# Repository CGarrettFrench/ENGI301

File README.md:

<h1>ENGI301</h1>
Repository for ENGI301 coursework

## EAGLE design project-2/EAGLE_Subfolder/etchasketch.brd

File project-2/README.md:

# ENGI 301 Project 02
# Garrett French
# ENGI 301 F22

This folder contains my submission for Project 02 for ENGI 301 F22, which is a design of a PCB board for a standard Etch-a-Sketch developed on a PocketBeagle platform. Within this folder is a .pdf file of my schematic ("schematicpdf"), the Bill of Materials for my design ("etchasketchBOM"), an "mfg" sub-folder containing my manufacturing gerber files generated by Eagle, a "docs" sub-folder containing my mechanical diagram and screenshots of the top and bottom layer of my PCB board, and finally, an "EAGLE_Subfolder" sub-folder which contains the Eagle files for this design - the schematic, library, board, and design rules files.

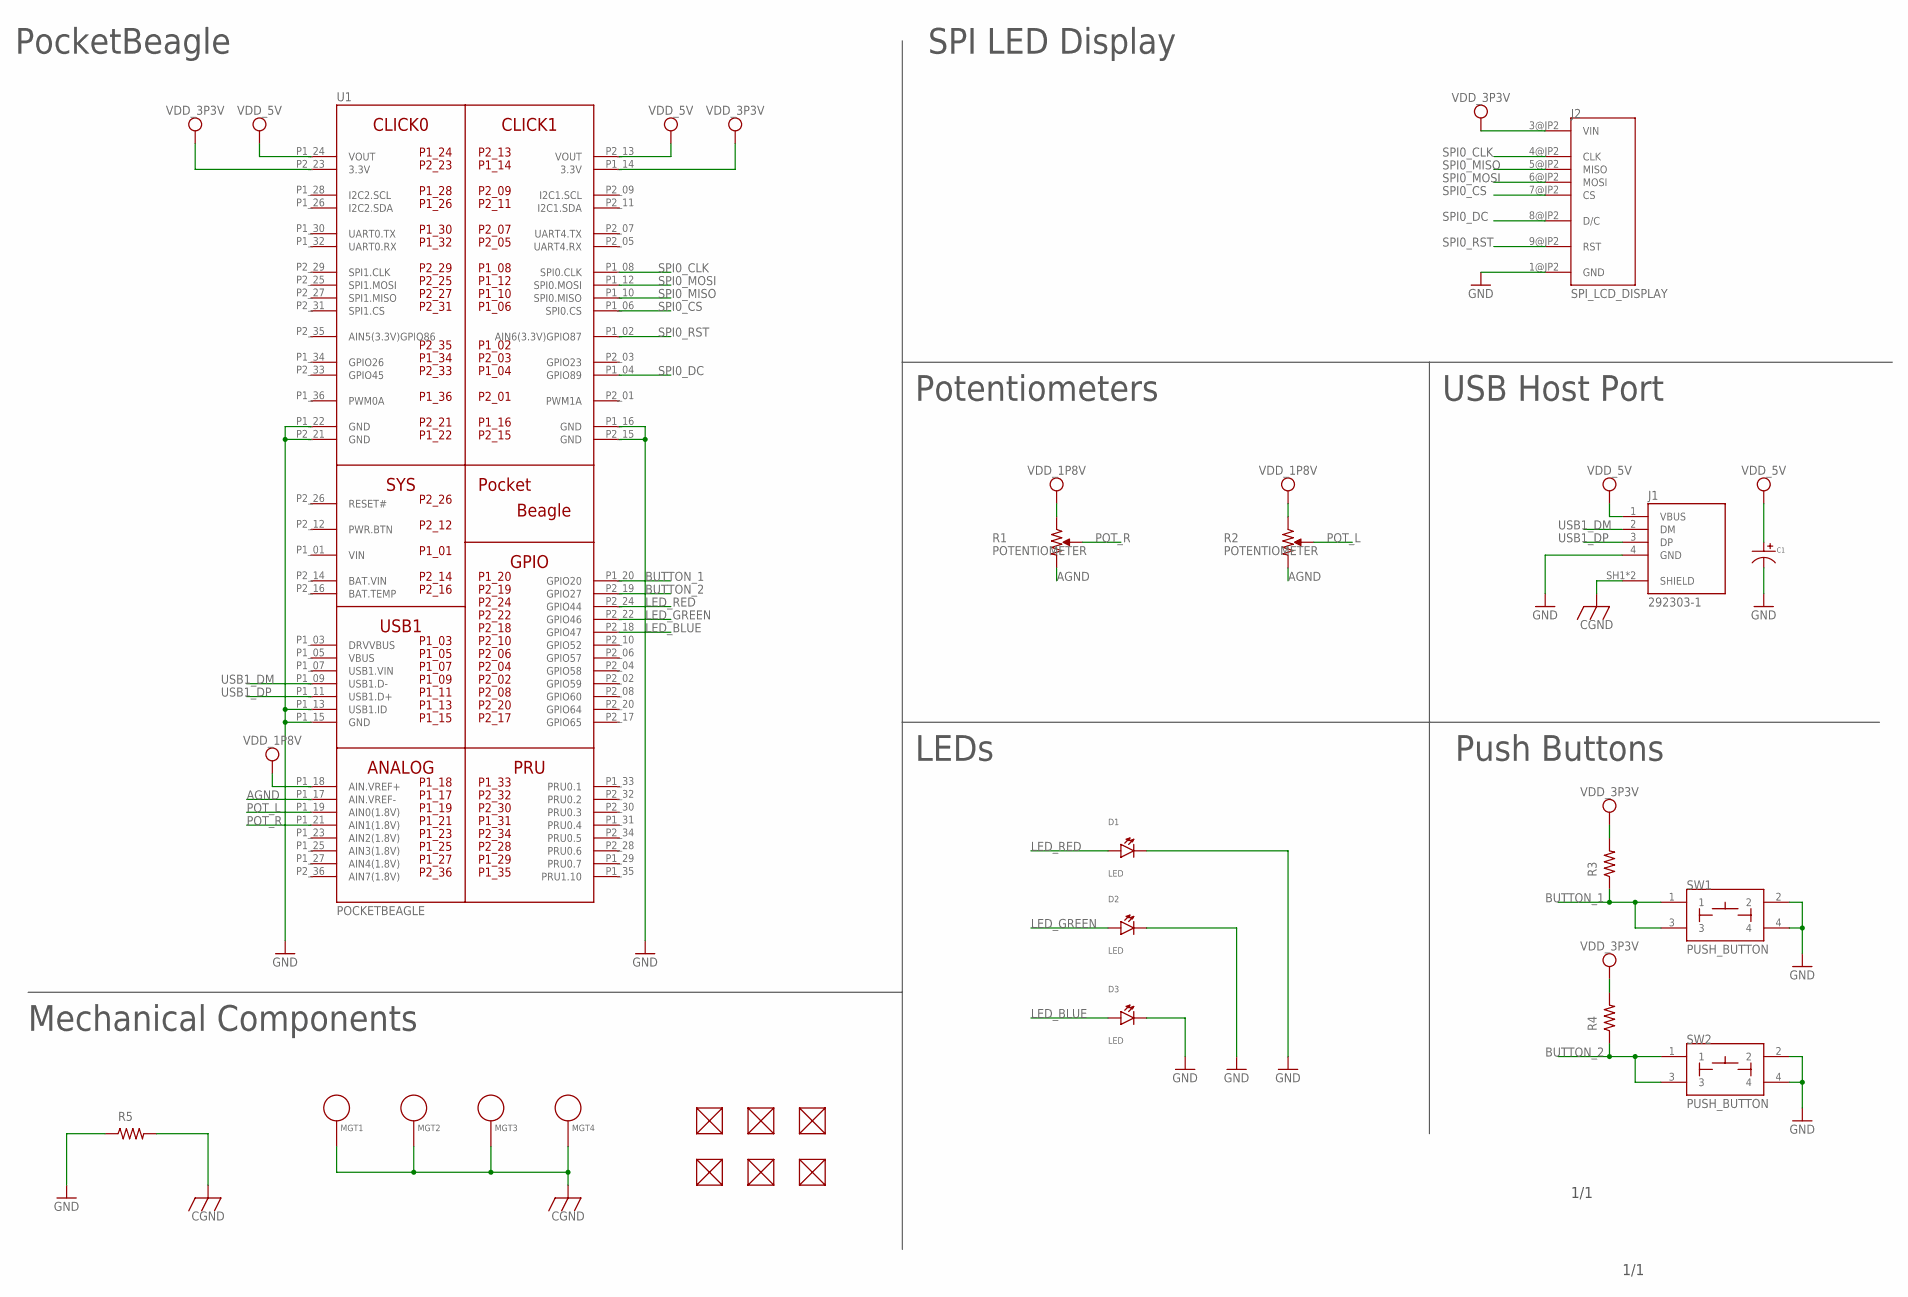
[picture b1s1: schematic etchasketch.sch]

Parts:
C1: CAPACITOR_P_10MM; CP10MM
D1, D2, D3: LED; EIA-STD
FUD1, FUD2, FUD3, FUD4, FUD5, FUD6: FIDUCIAL; FIDUCIAL_40MIL
J1: 292303-1; TE_292303-1
J2: SPI_LCD_DISPLAY; TFT_LCD_PCB
MGT1, MGT2, MGT3, MGT4: MOUNTING_HOLE
R1, R2: POTENTIOMETER; POT-PO90S
R3, R4, R5: R_R0603; R0603
SW1, SW2: PUSH_BUTTON; BUTTON_12.5MM
U1: POCKETBEAGLE

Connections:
AGND: R1.CW, R2.CW, U1.P1_17 (AIN.VREF-)
BAT.VIN: U1.P2_14 (BAT.VIN)
BUTTON_1: R3.1, SW1.1, SW1.3, U1.P1_20 (GPIO20)
BUTTON_2: R4.1, SW2.1, SW2.3, U1.P2_19 (GPIO27)
CGND: J1.SH1 (SHIELD), J1.SH2 (SHIELD), MGT1.P$1, MGT2.P$1, MGT3.P$1, MGT4.P$1, R5.2
GND: C1.P$2, D1.CATHODE, D2.CATHODE, D3.CATHODE, J1.4 (GND), J2.1@JP2 (GND), R5.1, SW1.2, SW1.4, SW2.2, SW2.4, U1.P1_13 (USB1.ID), U1.P1_15 (GND), U1.P1_16 (GND), U1.P1_22 (GND), U1.P2_15 (GND), U1.P2_21 (GND)
LED_BLUE: D3.ANODE, U1.P2_18 (GPIO47)
LED_GREEN: D2.ANODE, U1.P2_22 (GPIO46)
LED_RED: D1.ANODE, U1.P2_24 (GPIO44)
POT_L: R2.S, U1.P1_19 (AIN0(1.8V))
POT_R: R1.S, U1.P1_21 (AIN1(1.8V))
SPI0_CLK: J2.4@JP2 (CLK), U1.P1_08 (SPI0.CLK)
SPI0_CS: J2.7@JP2 (CS), U1.P1_06 (SPI0.CS)
SPI0_DC: J2.8@JP2 (D/C), U1.P1_04 (GPIO89)
SPI0_MISO: J2.5@JP2 (MISO), U1.P1_10 (SPI0.MISO)
SPI0_MOSI: J2.6@JP2 (MOSI), U1.P1_12 (SPI0.MOSI)
SPI0_RST: J2.9@JP2 (RST), U1.P1_02 (AIN6(3.3V)GPIO87)
USB1_DM: J1.2 (DM), U1.P1_09 (USB1.D-)
USB1_DP: J1.3 (DP), U1.P1_11 (USB1.D+)
VDD_1P8V: R1.CCW, R2.CCW, U1.P1_18 (AIN.VREF+)
VDD_3P3V: J2.3@JP2 (VIN), R3.2, R4.2, U1.P1_14 (3.3V), U1.P2_23 (3.3V)
VDD_5V: C1.P$1, J1.1 (VBUS), U1.P1_24 (VOUT), U1.P2_13 (VOUT)
VIN: U1.P1_01 (VIN)

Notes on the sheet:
PocketBeagle
SPI LED Display
Potentiometers
USB Host Port
Push Buttons
LEDs
Mechanical Components
1/1

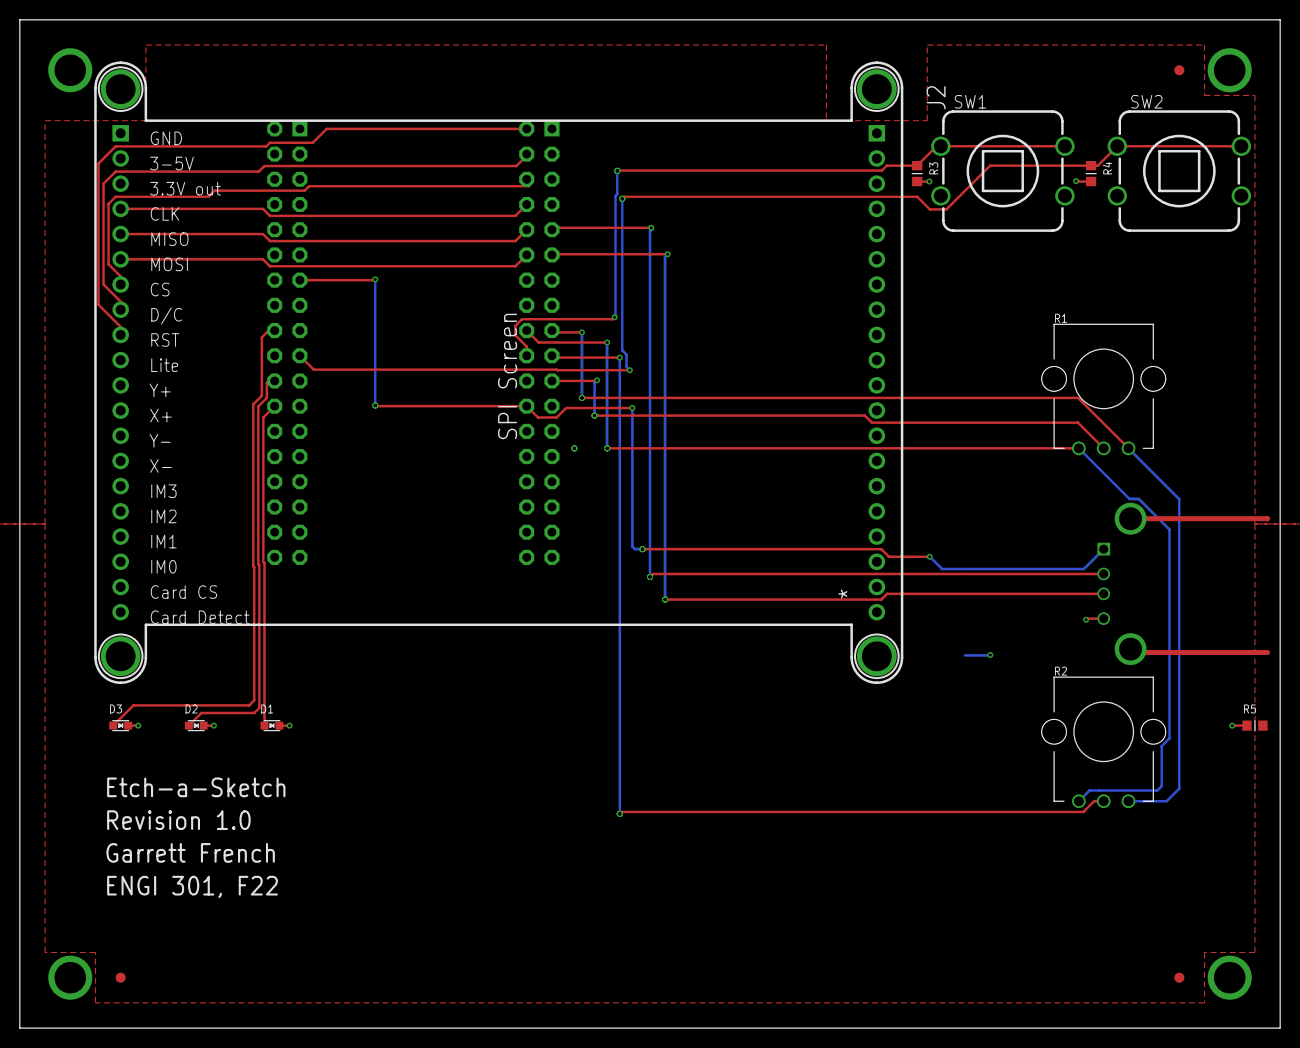
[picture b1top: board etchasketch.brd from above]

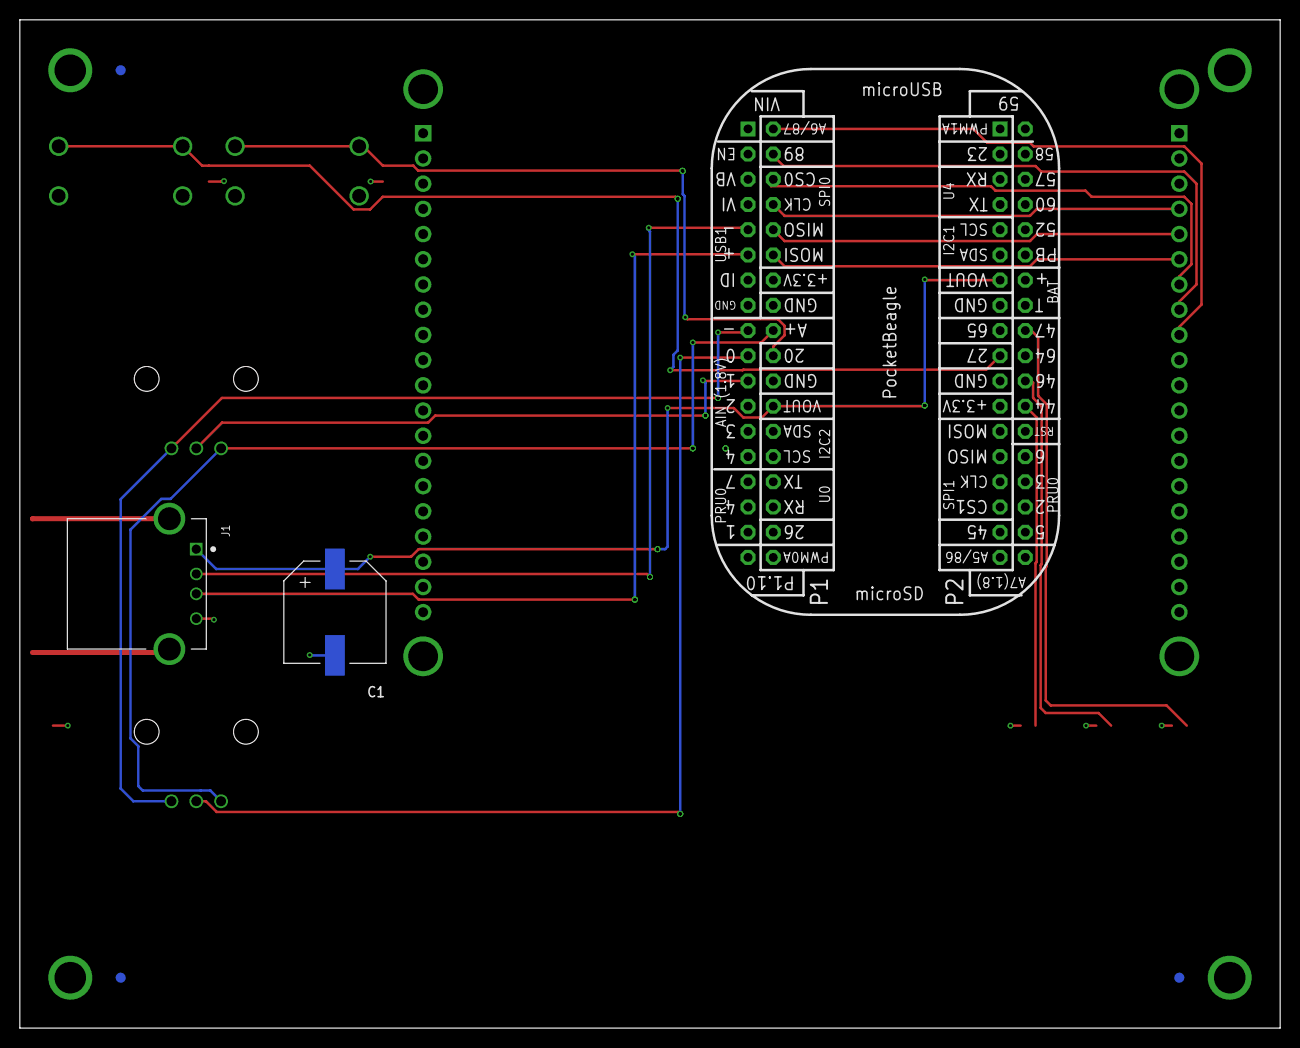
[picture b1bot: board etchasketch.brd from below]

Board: 4 copper layers, 127.0 x 101.6 mm, 24 parts (6 on the bottom side), 21 nets.

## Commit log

2022-09-08 Updating README.md
2022-09-08 Update README.md
    Updating README.md
2022-09-18 Committing simple calc to repository
2022-09-18 Committing simple calc with support for new operations
2022-09-24 Recommitting simple calc with a fixed header
2022-09-24 Committing my LED blinking program
2022-10-15 Create ENGI 301 Project Proposal.pdf
    Uploading project proposal
2022-12-12 project_02 submission 1
    project_02 submission 1
2022-12-13 project_01 submission
    project_01 submission
